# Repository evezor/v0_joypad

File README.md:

# Joypad Edge Board
*please note this board has been deprecated.

An edge board shaped like a joypad. It has 2 analog inputs, 4 light up buttons, start and select pushbuttons, a dpad, a buzzer and a 5 position neopixel strip. 

source files can be found here: https://github.com/evezor/v0_joypad

This board uses the Evezor Stamp STMF405 MCU

source: https://github.com/evezor/Evezor-Stamp-STMF405

Evezor® and all associated marks, logos, and designs are registered trademarks and protected by copyright. Unauthorized use or reproduction of these trademarks and copyrighted materials is strictly prohibited.

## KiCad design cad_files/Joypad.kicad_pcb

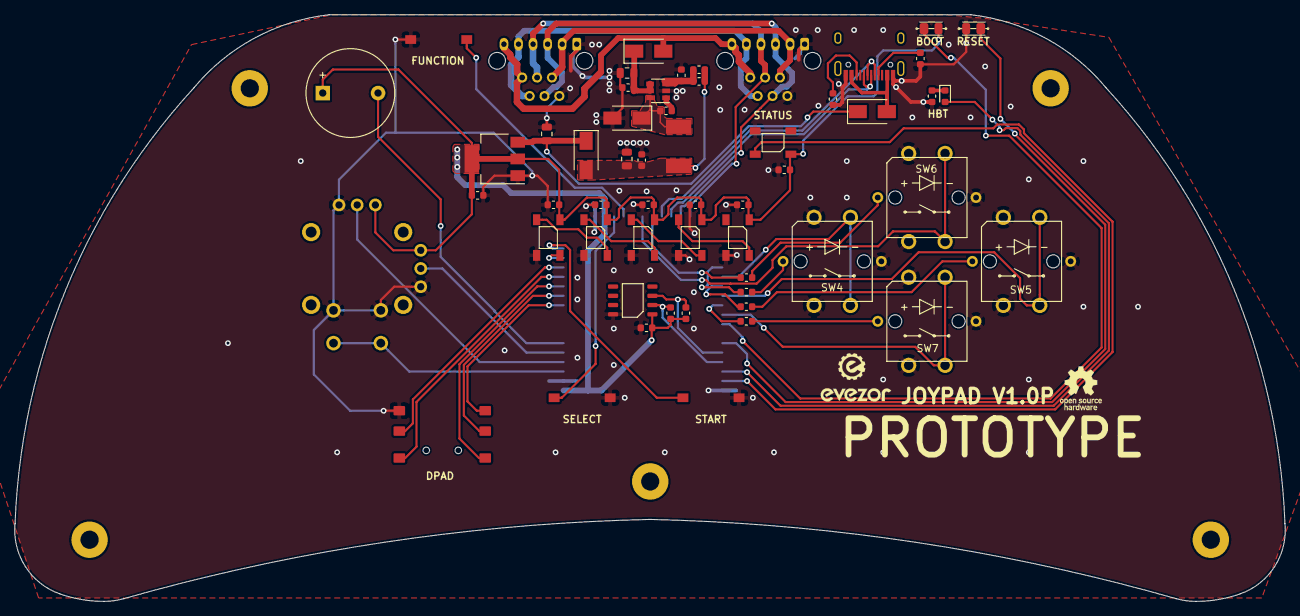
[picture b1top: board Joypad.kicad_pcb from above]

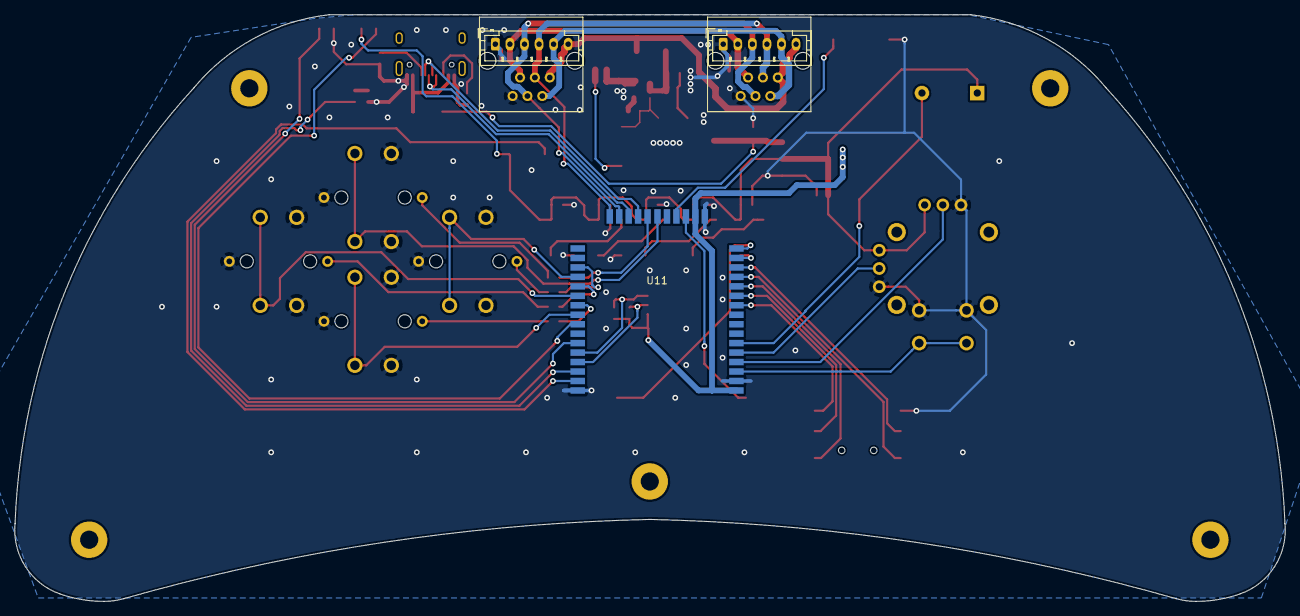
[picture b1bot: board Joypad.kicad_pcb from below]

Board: 2 copper layers, 174.5 x 80.6 mm, 64 parts (5 on the bottom side), 54 nets.

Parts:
BZ1: Buzzer; Buzzer_12x9.5RM7.6
C1, C2, C3, C5, C9, C14, C15: .1uF; C_0603_1608Metric
C4: 4.7uF; C_0805_2012Metric
C6: 22uF; C_0805_2012Metric
C7, C8, C10, C11, C12: 100nF; C_0603_1608Metric
C13: 10uF; C_0805_2012Metric
D1, D2, D4, D5: D_Schottky; D_SMA
D3: LED; LED_0603_1608Metric
H1, H2, H3, H4, H5: MountingHole; MountingHole_2.5mm_Pad
J1: USB_C_Receptacle_USB2.0; USB_C_Receptacle_HRO_TYPE-C-31-M-12
J2, J3: RJ11; RJ11_C189747_Horizontal
J4, J5: PH; JST_PH_B6B-PH-K_1x06_P2.00mm_Vertical
JP1: BOOT; SHORT_PAD
JP2: RESET; SHORT_PAD
L1: 22uH; INDUCTOR_7.5X6.6_GCDA0630-220MC
R1, R5: 15k; R_0603_1608Metric
R2: 82k; R_0603_1608Metric
R3, R4, R6, R7: UNKN; R_0603_1608Metric
R8, R9: 5.1k; R_0603_1608Metric
R10, R11: 4.7k; R_0603_1608Metric
SW2, SW3, SW8: SW_Push; SWITCH_2x3_SMD_TACTILE_GREEN
SW4: GRN_BUTTON_ILLUMINATED_12x12; Illuminated_Round_Button
SW5: BLU_BUTTON_ILLUMINATED_12x12; Illuminated_Round_Button
SW6: RED_BUTTON_ILLUMINATED_12x12; Illuminated_Round_Button
SW7: YEL_BUTTON_ILLUMINATED_12x12; Illuminated_Round_Button
U1: V_REG; SOT-23-6
U2: AMS1117-3.3; SOT-223-3_TabPin2
U3: SWITCH_5-WAY_TACTIL_10X10; SWITCH_5WAY_10x10
U4, U5, U6, U7, U8, U9: NEOPIXEL_5050
U10: JOYSTICK
U11: EDGE_STM32F405_CPU_V1; EDGE_STAMP
U12: MICOCONTROLLER_GUID_SOP-8; GUID_PS150C

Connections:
+3V3: BZ1.1, C7.2, C8.2, C9.1, C10.2, C11.2, C12.2, C14.2, C15.2, JP1.2, R10.1, R11.1, U2.2, U4.1, U5.1, U6.1, U7.1, U8.1, U9.1, U10.4, U11.1, U11.18, U12.1
+48V: D2.2, J2.6, J3.6, J4.6, J5.6
/5WAY_DOWN: U3.6, U11.12
/5WAY_LEFT: U3.2, U11.14
/5WAY_PUSH: U3.3, U11.13
/5WAY_RIGHT: U3.5, U11.11
/5WAY_UP: U3.4, U11.10
/BLU_BUT: SW5.1, U11.33
/BLU_BUT_LED: R4.2, U11.32
/BOOT: JP1.1, U11.36
/BUZZER: BZ1.2, U11.6
/CAN_H: J2.3, J3.3, J4.3, J5.3, U11.26
/CAN_L: J2.4, J3.4, J4.4, J5.4, U11.27
/D+: J1.A6, J1.B6, U11.25
/D-: J1.A7, J1.B7, U11.24
/FD_H: J2.2, J3.2, J4.2, J5.2
/FD_L: J2.5, J3.5, J4.5, J5.5
/FUNCTION: SW8.1, U11.20
/GRN_BUT: SW4.1, U11.31
/GRN_BUT_LED: R3.2, U11.30
/GUID_SDA: R11.2, U11.39, U12.3
/GUID_SDO: R10.2, U11.40, U12.2
/JOY_SW: U10.3, U11.3
/JOY_X: U10.1, U11.4
/JOY_Y: U10.2, U11.5
/NEO_STATUS: U6.4, U11.42
/NEO_STRIP: U4.4, U11.15
/RED_BUT: SW6.1, U11.22
/RED_BUT_LED: R6.2, U11.23
/RESET: JP2.1, U11.38
/SELECT: SW3.1, U11.19
/START: SW2.1, U11.16
/USB_VCC: D4.2, J1.A4, J1.A9, J1.B4, J1.B9
/VREG: C2.1, C5.1, C6.1, D5.2, L1.2, R2.1
/YEL_BUT: SW7.1, U11.35
/YEL_BUT_LED: R7.2, U11.34
GND: C3.2, C4.2, C5.2, C6.2, C7.1, C8.1, C9.2, C10.1, C11.1, C12.1, C13.1, C14.1, C15.1, D1.2, J1.A1, J1.A12, J1.B1, J1.B12, J2.1, J3.1, J4.1, J5.1, JP2.2, R1.1, R5.1, R8.2, R9.2, SW2.2, SW3.2, SW4.2, SW4.4, SW5.2, SW5.4, SW6.2, SW6.4, SW7.2, SW7.4, SW8.2, U1.2, U2.1, U3.1, U4.3, U5.3, U6.3, U7.3, U8.3, U9.3, U10.5, U11.2, U11.17, U11.43, U12.8
unnamed: C1.1, D1.1, L1.1, U1.6
unnamed: C1.2, U1.1
unnamed: C2.2, R1.2, R2.2, U1.3
unnamed: C3.1, C4.1, D2.1, U1.4, U1.5
unnamed: C13.2, D4.1, D5.1, U2.3
unnamed: D3.1, R5.2
unnamed: D3.2, U11.41
unnamed: J1.A5, R9.1
unnamed: J1.B5, R8.1
unnamed: R3.1, SW4.3
unnamed: R4.1, SW5.3
unnamed: R6.1, SW6.3
unnamed: R7.1, SW7.3
unnamed: U4.2, U5.4
unnamed: U5.2, U7.4
unnamed: U7.2, U8.4
unnamed: U8.2, U9.4

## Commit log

2020-11-06 inital commit
2023-09-11 add pics
